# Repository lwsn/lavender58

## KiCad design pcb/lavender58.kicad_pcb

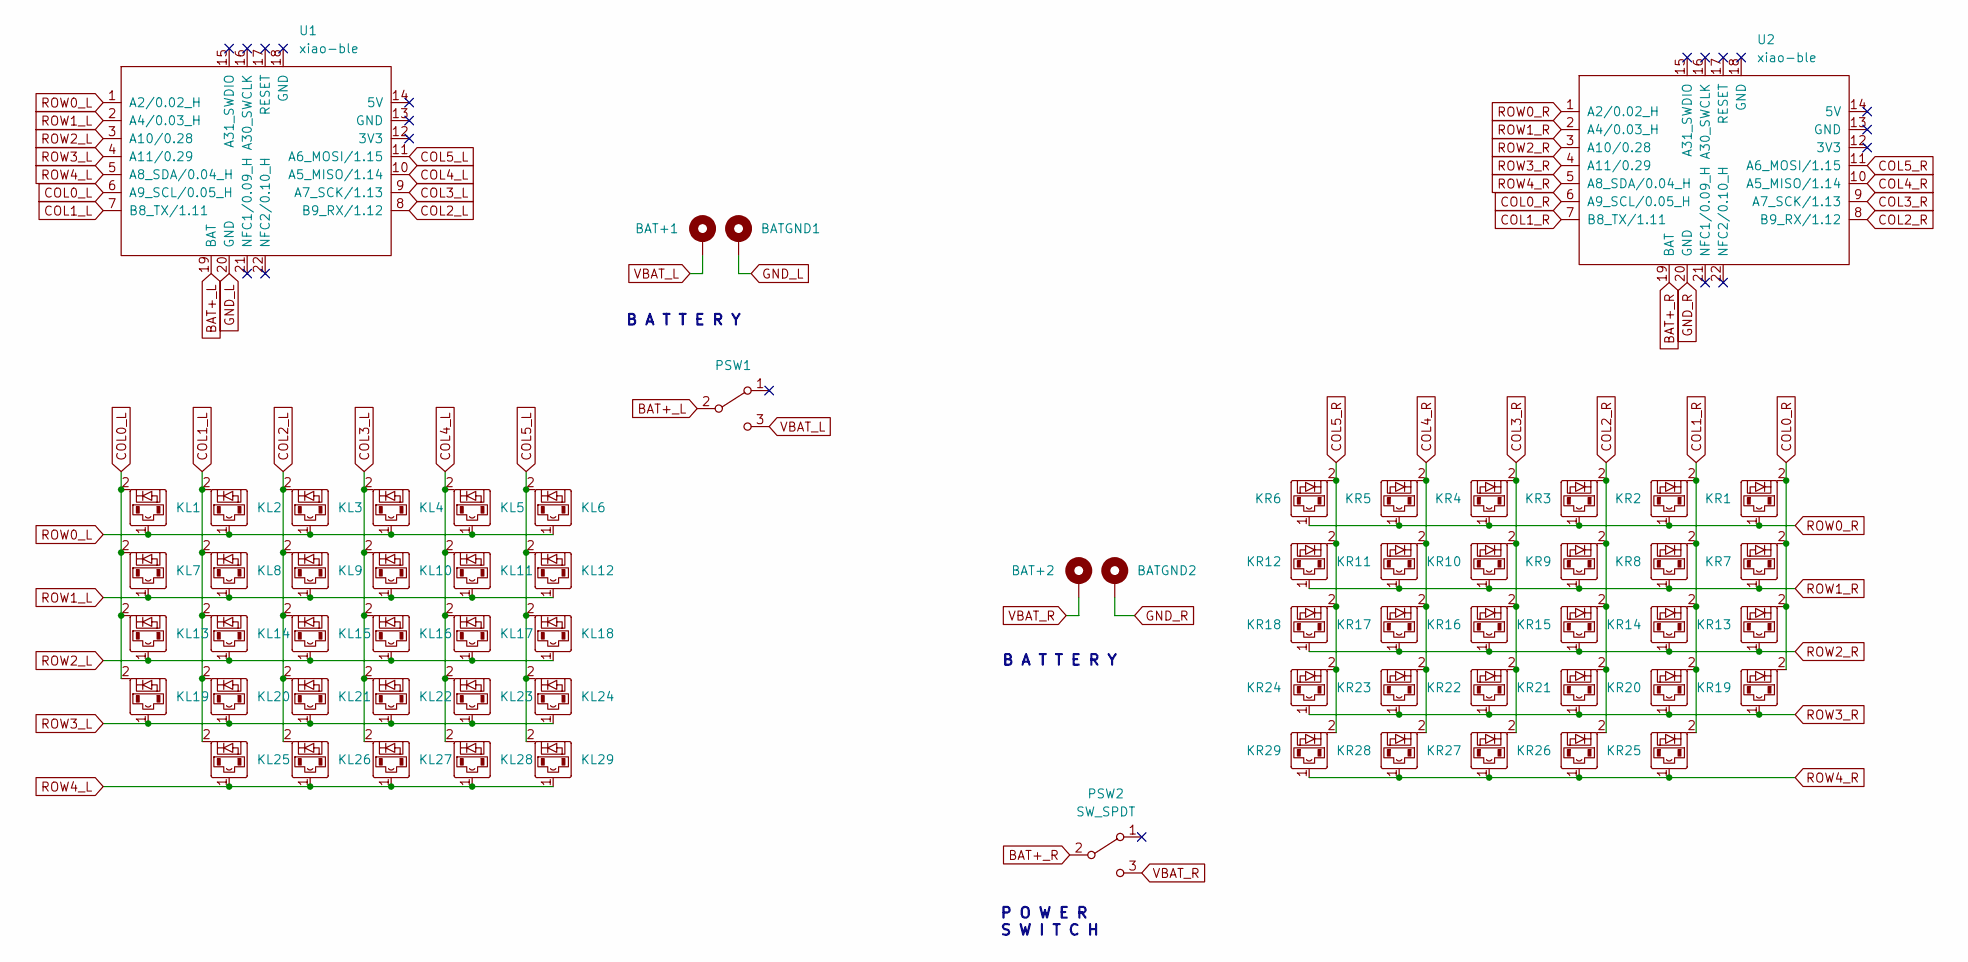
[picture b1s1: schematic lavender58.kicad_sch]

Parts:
BAT+1, BAT+2: +; SolderWirePad_1x01_SMD_1.5x3mm
BATGND1, BATGND2: -; SolderWirePad_1x01_SMD_1.5x3mm
KL1, KL2, KL3, KL4, KL5, KL6, KL7, KL8, KL9, KL10, KL11, KL12, KL13, KL14, KL15, KL16, KL17, KL18, KL19, KL20, KL21, KL22, KL23, KL24, KL25, KL26, KL27, KL28, KL29: diode-choc; pg1350-D
KR1, KR2, KR3, KR4, KR5, KR6, KR7, KR8, KR9, KR10, KR11, KR12, KR13, KR14, KR15, KR16, KR17, KR18, KR19, KR20, KR21, KR22, KR23, KR24, KR25, KR26, KR27, KR28, KR29: diode-choc; pg1350-D
PSW1, PSW2: SW_SPDT; CUS-12TB_NDC
U1, U2: xiao-ble; xiao-ble-smd-cutout

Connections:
BAT+_L: PSW1.2 (B), U1.19 (BAT)
BAT+_R: PSW2.2 (B), U2.19 (BAT)
COL0_L: KL1.2, KL7.2, KL13.2, KL19.2, U1.6 (A9_SCL/0.05_H)
COL0_R: KR1.2, KR7.2, KR13.2, KR19.2, U2.6 (A9_SCL/0.05_H)
COL1_L: KL2.2, KL8.2, KL14.2, KL20.2, KL25.2, U1.7 (B8_TX/1.11)
COL1_R: KR2.2, KR8.2, KR14.2, KR20.2, KR25.2, U2.7 (B8_TX/1.11)
COL2_L: KL3.2, KL9.2, KL15.2, KL21.2, KL26.2, U1.8 (B9_RX/1.12)
COL2_R: KR3.2, KR9.2, KR15.2, KR21.2, KR26.2, U2.8 (B9_RX/1.12)
COL3_L: KL4.2, KL10.2, KL16.2, KL22.2, KL27.2, U1.9 (A7_SCK/1.13)
COL3_R: KR4.2, KR10.2, KR16.2, KR22.2, KR27.2, U2.9 (A7_SCK/1.13)
COL4_L: KL5.2, KL11.2, KL17.2, KL23.2, KL28.2, U1.10 (A5_MISO/1.14)
COL4_R: KR5.2, KR11.2, KR17.2, KR23.2, KR28.2, U2.10 (A5_MISO/1.14)
COL5_L: KL6.2, KL12.2, KL18.2, KL24.2, KL29.2, U1.11 (A6_MOSI/1.15)
COL5_R: KR6.2, KR12.2, KR18.2, KR24.2, KR29.2, U2.11 (A6_MOSI/1.15)
GND_L: BATGND1.1, U1.20 (GND); also elsewhere on the board
GND_R: BATGND2.1, U2.20 (GND); also elsewhere on the board
ROW0_L: KL1.1, KL2.1, KL3.1, KL4.1, KL5.1, KL6.1, U1.1 (A2/0.02_H)
ROW0_R: KR1.1, KR2.1, KR3.1, KR4.1, KR5.1, KR6.1, U2.1 (A2/0.02_H)
ROW1_L: KL7.1, KL8.1, KL9.1, KL10.1, KL11.1, KL12.1, U1.2 (A4/0.03_H)
ROW1_R: KR7.1, KR8.1, KR9.1, KR10.1, KR11.1, KR12.1, U2.2 (A4/0.03_H)
ROW2_L: KL13.1, KL14.1, KL15.1, KL16.1, KL17.1, KL18.1, U1.3 (A10/0.28)
ROW2_R: KR13.1, KR14.1, KR15.1, KR16.1, KR17.1, KR18.1, U2.3 (A10/0.28)
ROW3_L: KL19.1, KL20.1, KL21.1, KL22.1, KL23.1, KL24.1, U1.4 (A11/0.29)
ROW3_R: KR19.1, KR20.1, KR21.1, KR22.1, KR23.1, KR24.1, U2.4 (A11/0.29)
ROW4_L: KL25.1, KL26.1, KL27.1, KL28.1, KL29.1, U1.5 (A8_SDA/0.04_H)
ROW4_R: KR25.1, KR26.1, KR27.1, KR28.1, KR29.1, U2.5 (A8_SDA/0.04_H)
VBAT_L: BAT+1.1, PSW1.3 (C); also elsewhere on the board
VBAT_R: BAT+2.1, PSW2.3 (C); also elsewhere on the board

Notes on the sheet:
B A T T E R Y
P O W E R S W I T C H

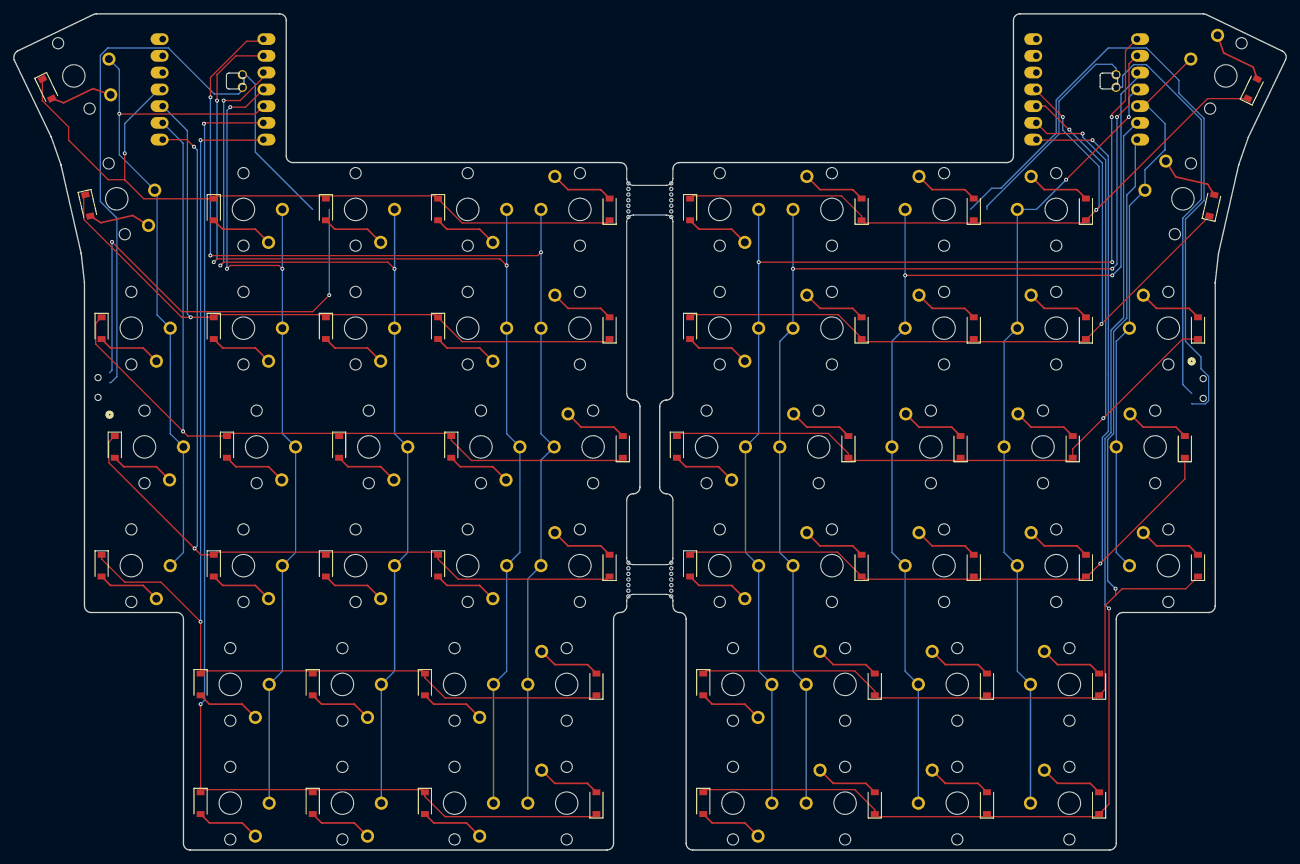
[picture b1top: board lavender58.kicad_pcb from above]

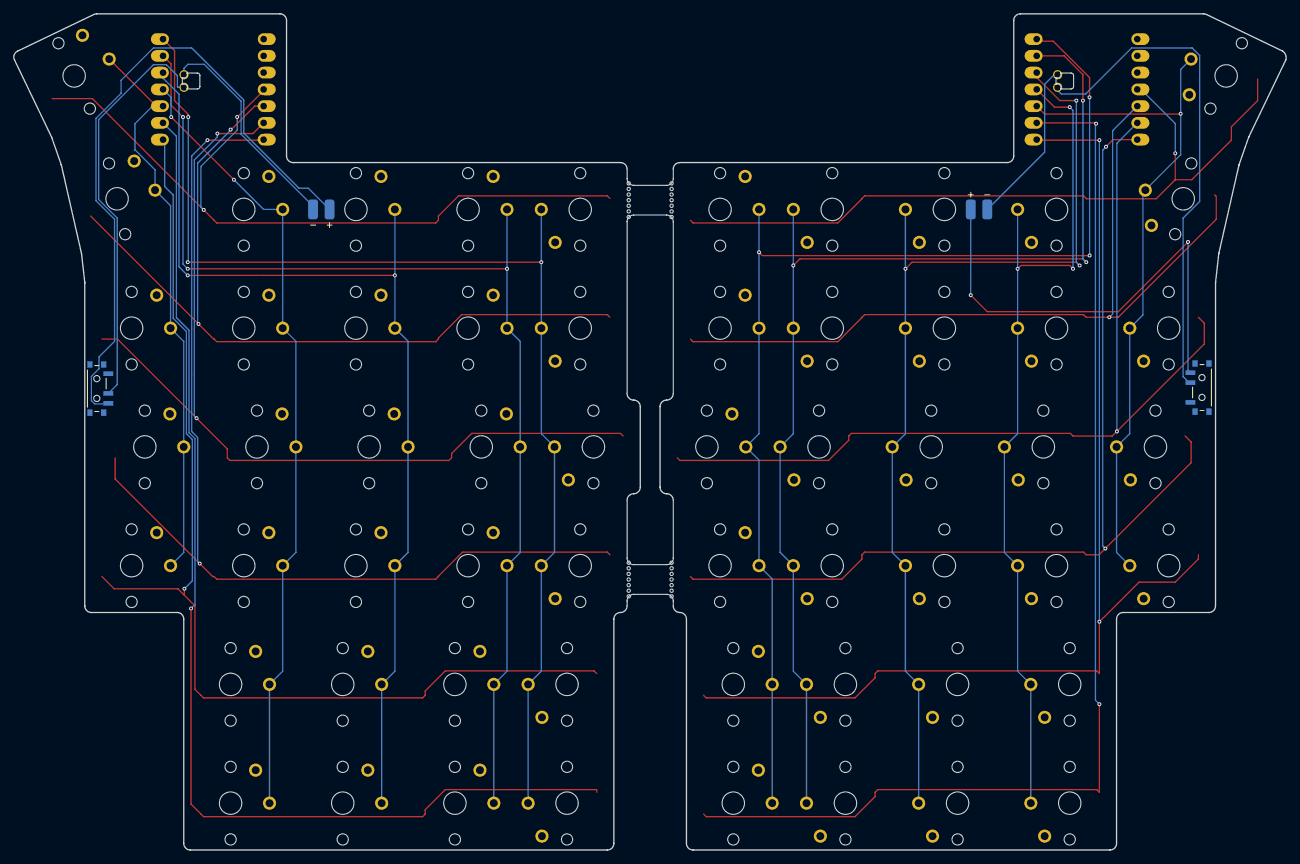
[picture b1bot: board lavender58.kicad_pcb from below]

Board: 2 copper layers, 192.9 x 126.7 mm, 66 parts (8 on the bottom side), 28 nets.

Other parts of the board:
+: +; SolderWirePad_1x01_SMD_1.5x3mm
+#2: +; SolderWirePad_1x01_SMD_1.5x3mm
-: -; SolderWirePad_1x01_SMD_1.5x3mm
-#2: -; SolderWirePad_1x01_SMD_1.5x3mm

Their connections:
GND_L: -.1; also elsewhere on the board
GND_R: -#2.1; also elsewhere on the board
VBAT_L: +.1; also elsewhere on the board
VBAT_R: +#2.1; also elsewhere on the board

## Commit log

2022-08-18 Initial User Config.
2022-09-13 WIP Left side
2022-09-17 Implements lavender58 split board
2022-09-18 Keymap
2022-10-20 Seeed
2023-11-23 Correct build
2023-11-23 Adds battery info
2023-11-23 Adds settings reset to seeed
2025-09-19 Moves zmk config into separate dir
2025-09-19 Uses zmk-supported naming scheme
2025-09-19 Moves build yaml to root
2025-09-22 Footprint and symbol cleanup
2025-09-22 wip lavender58 board
2025-09-24 finished lavender58 board
2025-09-24 Adds missing footprints
2025-09-24 setup git ignore
2025-09-26 moves folders
2025-09-26 Moves west.yml
2025-09-26 Restores original config structure
2025-09-29 old battery read
2025-09-29 Fixes broken config
2025-10-04 adds battery sensor, fixes column order
2025-10-04 adds prebuilt firmware
